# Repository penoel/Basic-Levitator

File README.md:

# Basic-Levitator
Two 40 kHz transducers that create a standing wave when positioned above each other.  They are driven with a 555 timer in astable mode.  A 3d printed part with a threaded heat insert is used to secure it to the board.

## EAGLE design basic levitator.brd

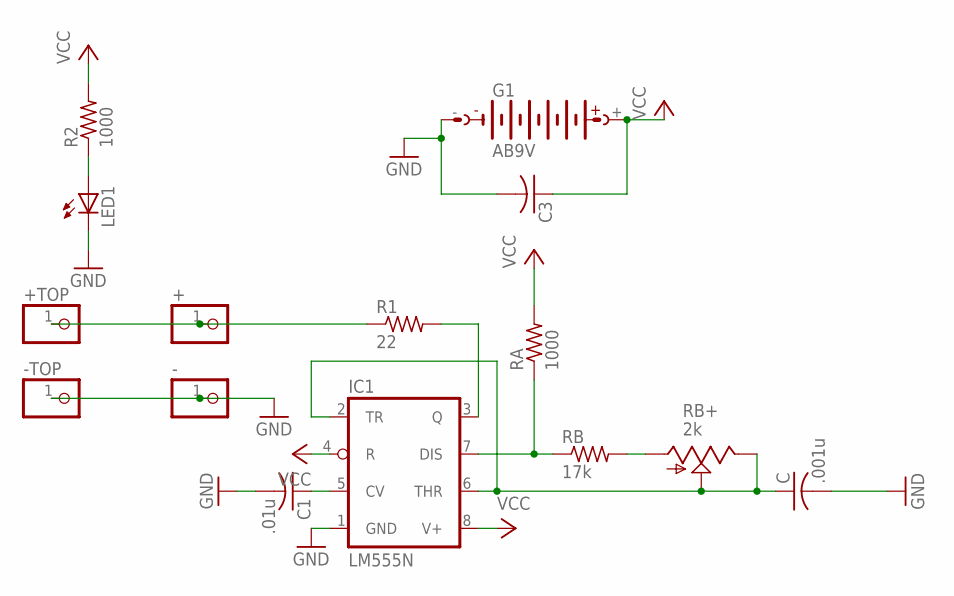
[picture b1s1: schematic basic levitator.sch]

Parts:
+: PINHD-1X1; 1X01
+TOP: PINHD-1X1; 1X01
-: PINHD-1X1; 1X01
-TOP: PINHD-1X1; 1X01
C: .001u; C025-024X044
C1: .01u; C025-025X050
C3: C-US050-024X044; C050-024X044
G1: AB9V
IC1: LM555N; DIL08
LED1: LED3MM
R1: 22; 0207/10
R2: 1000; 0207/10
RA: 1000; 0207/10
RB: 17k; 0207/10
RB+: 2k; CA6V

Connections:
GND: -.1, -TOP.1, C.2, C1.2, C3.2, G1.-, IC1.1 (GND), LED1.K (C)
unnamed: LED1.A, R2.1
unnamed: C1.1, IC1.5 (CV)
unnamed: C.1, IC1.2 (TR), IC1.6 (THR), RB+.E, RB+.S
unnamed: IC1.7 (DIS), RA.1, RB.1
unnamed: IC1.3 (Q), R1.2
unnamed: +.1, +TOP.1, R1.1
unnamed: RB.2, RB+.A
VCC: C3.1, G1.+, IC1.4 (R), IC1.8 (V+), R2.2, RA.2

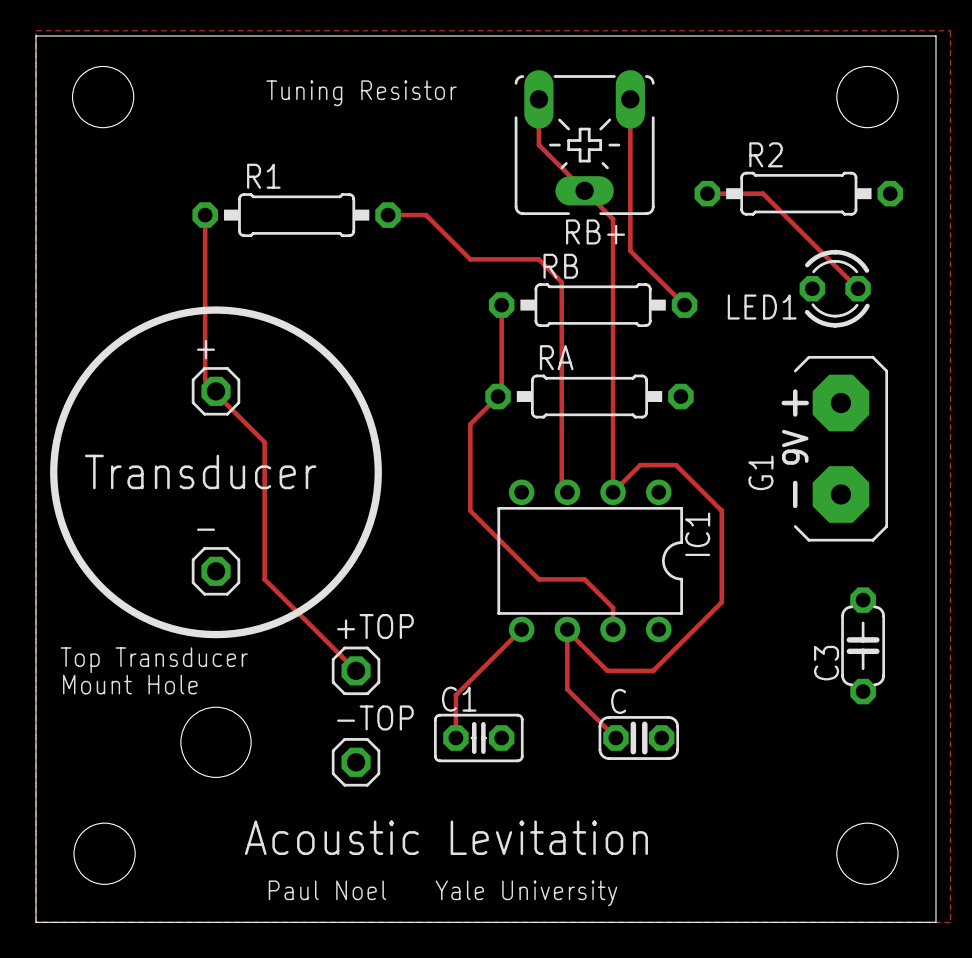
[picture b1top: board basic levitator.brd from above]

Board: 2 copper layers, 50.0 x 49.2 mm, 15 parts (0 on the bottom side), 9 nets.
